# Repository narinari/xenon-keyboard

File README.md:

# xenon-keyboard
Xenon is 60% columnar staggered keyboard.

## xenon-classic

Full feature version Xenon
- Cherry MX and Kailh low profile key switch support
- OLED display
- Full color LED
- Prototype board area (behind the promicro)

Xenon with Godspeed custom SA keycap

Xenon with MiTo GMK Laser custom keycap

Xenon with MDA BigBang and 3D printed keycap

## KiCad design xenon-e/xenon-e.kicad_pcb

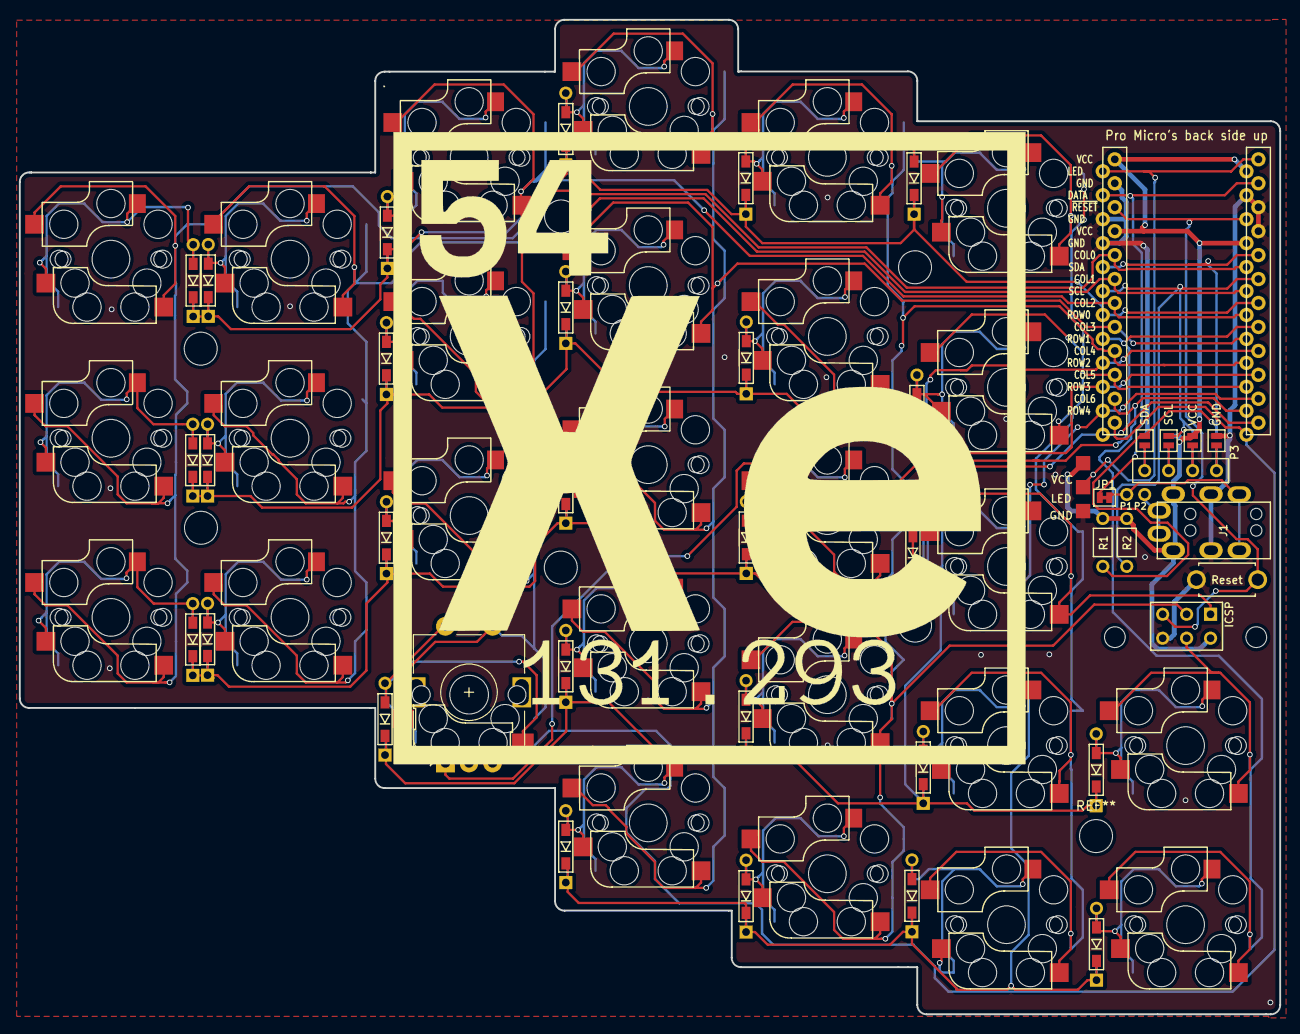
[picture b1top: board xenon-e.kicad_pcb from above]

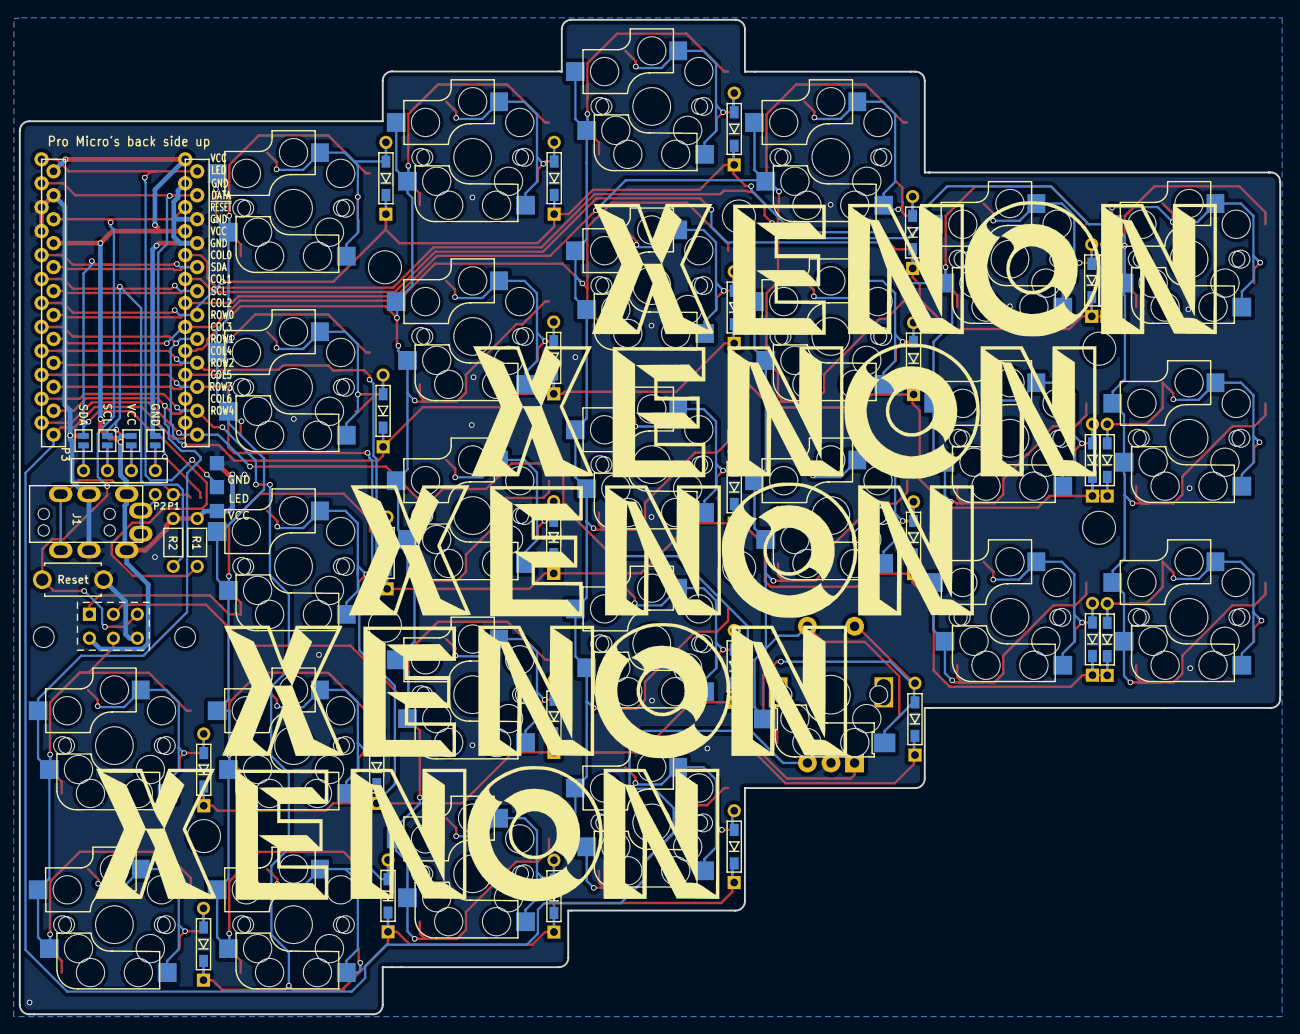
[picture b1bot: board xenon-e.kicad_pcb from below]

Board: 2 copper layers, 133.7 x 105.5 mm, 81 parts (5 on the bottom side), 54 nets.

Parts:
D1, D2, D3, D4, D5, D6, D7, D8, D9, D10, D11, D12, D13, D14, D15, D16, D17, D18, D21, D22, D23, D24, D25, D29, D30, D31, D32: D; D3_TH_SMD
J1: MJ-4PP-9; MJ-4PP-9_rev2
JP1: JPC2
JP4, JP11: GND; Jumper
JP5, JP10: VCC; Jumper
JP6, JP9: SCL; Jumper
JP7, JP8: SDA; Jumper
P1, P2: CONN_01X01; 1PIN_0.1
P3: OLED; MY_SIL-4
P4: LED; StripLED_rev
P5: ICSP; MY_SIL-2x3
R1, R2: R; R2
Ref**: Val**; MountingHole_3.5mm
Ref**#2, Ref**#3, Ref**#4, Ref**#5, Ref**#6: Val**; MountingHole_3.5mm
SW1, SW2, SW3, SW4, SW5, SW6, SW7, SW8, SW9, SW10, SW11, SW12, SW13, SW14, SW15, SW16, SW17, SW18, SW22, SW23, SW24, SW25, SW29, SW30, SW31, SW32: SW_PUSH; CherryMX_Choc_Hotswap
SW21: SW_PUSH; CherryMX_Hotswap
SW33: Reset; SW_3.5x6.0_TH
SW34: Rotary_Encoder_Switch; RotaryEncoder_Alps_EC11E-Switch_Vertical_H20mm
U1, U1#2: ProMicro; ProMicro_rev

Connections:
/SCL: JP6.1, JP9.1, R2.2, U1.6, U1#2.6
/SDA: JP7.1, JP8.1, R1.2, U1.5, U1#2.5
/~RESET: P5.5, SW33.2, U1.22, U1#2.22
GND: J1.C, JP4.1, JP11.1, P4.3, P5.6, SW33.1, SW34.C, U1.3, U1.4, U1.23, U1#2.3, U1#2.4, U1#2.23
LED: P4.2, U1.1, U1#2.1
unnamed: D1.2, SW1.2
unnamed: D2.2, SW2.2
unnamed: D3.2, SW3.2
unnamed: D4.2, SW4.2
unnamed: D5.2, SW5.2
unnamed: D6.2, SW6.2
unnamed: D7.2, SW7.2
unnamed: D8.2, SW8.2
unnamed: D9.2, SW9.2
unnamed: D10.2, SW10.2
unnamed: D11.2, SW11.2
unnamed: D12.2, SW12.2
unnamed: D13.2, SW13.2
unnamed: D14.2, SW14.2
unnamed: D15.2, SW15.2
unnamed: D16.2, SW16.2
unnamed: D17.2, SW17.2
unnamed: D18.2, SW18.2
unnamed: D21.2, SW21.2, SW34.S2
unnamed: D22.2, SW22.2
unnamed: D23.2, SW23.2
unnamed: D24.2, SW24.2
unnamed: D25.2, SW25.2
unnamed: D29.2, SW29.2
unnamed: D30.2, SW30.2
unnamed: D31.2, SW31.2
unnamed: D32.2, SW32.2
unnamed: J1.A, P2.1
unnamed: J1.B, JP1.2, P1.1
unnamed: JP4.2, JP8.2, P3.1
unnamed: JP5.2, JP9.2, P3.2
unnamed: JP6.2, JP10.2, P3.3
unnamed: JP7.2, JP11.2, P3.4
ROTARY_A: SW34.A, U1.12, U1#2.12
ROTARY_B: SW34.B, U1.13, U1#2.13
VCC: J1.D, JP5.1, JP10.1, P4.1, P5.2, R1.1, R2.1, U1.21, U1.24, U1#2.21, U1#2.24
col0: SW1.1, SW7.1, SW13.1, U1.20, U1#2.20
col1: SW2.1, SW8.1, SW14.1, U1.19, U1#2.19
col2: SW3.1, SW9.1, SW15.1, SW21.1, SW34.S1, U1.18, U1#2.18
col3: SW4.1, SW10.1, SW16.1, SW22.1, SW29.1, U1.17, U1#2.17
col4: P5.3, SW5.1, SW11.1, SW17.1, SW23.1, SW30.1, U1.16, U1#2.16
col5: P5.1, SW6.1, SW12.1, SW18.1, SW24.1, SW31.1, U1.15, U1#2.15
col6: P5.4, SW25.1, SW32.1, U1.14, U1#2.14
data: JP1.1, U1.2, U1#2.2
row0: D1.1, D2.1, D3.1, D4.1, D5.1, D6.1, U1.7, U1#2.7
row1: D7.1, D8.1, D9.1, D10.1, D11.1, D12.1, U1.8, U1#2.8
row2: D13.1, D14.1, D15.1, D16.1, D17.1, D18.1, U1.9, U1#2.9
row3: D21.1, D22.1, D23.1, D24.1, D25.1, U1.10, U1#2.10
row4: D29.1, D30.1, D31.1, D32.1, U1.11, U1#2.11

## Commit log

2019-08-11 Add gerber files
2019-08-11 First Xenon-e pcb
2019-08-11 Add gerber files of plates
2019-08-11 Add plate data
2019-08-11 Add image of example
2019-09-16 Change mouting hole size
